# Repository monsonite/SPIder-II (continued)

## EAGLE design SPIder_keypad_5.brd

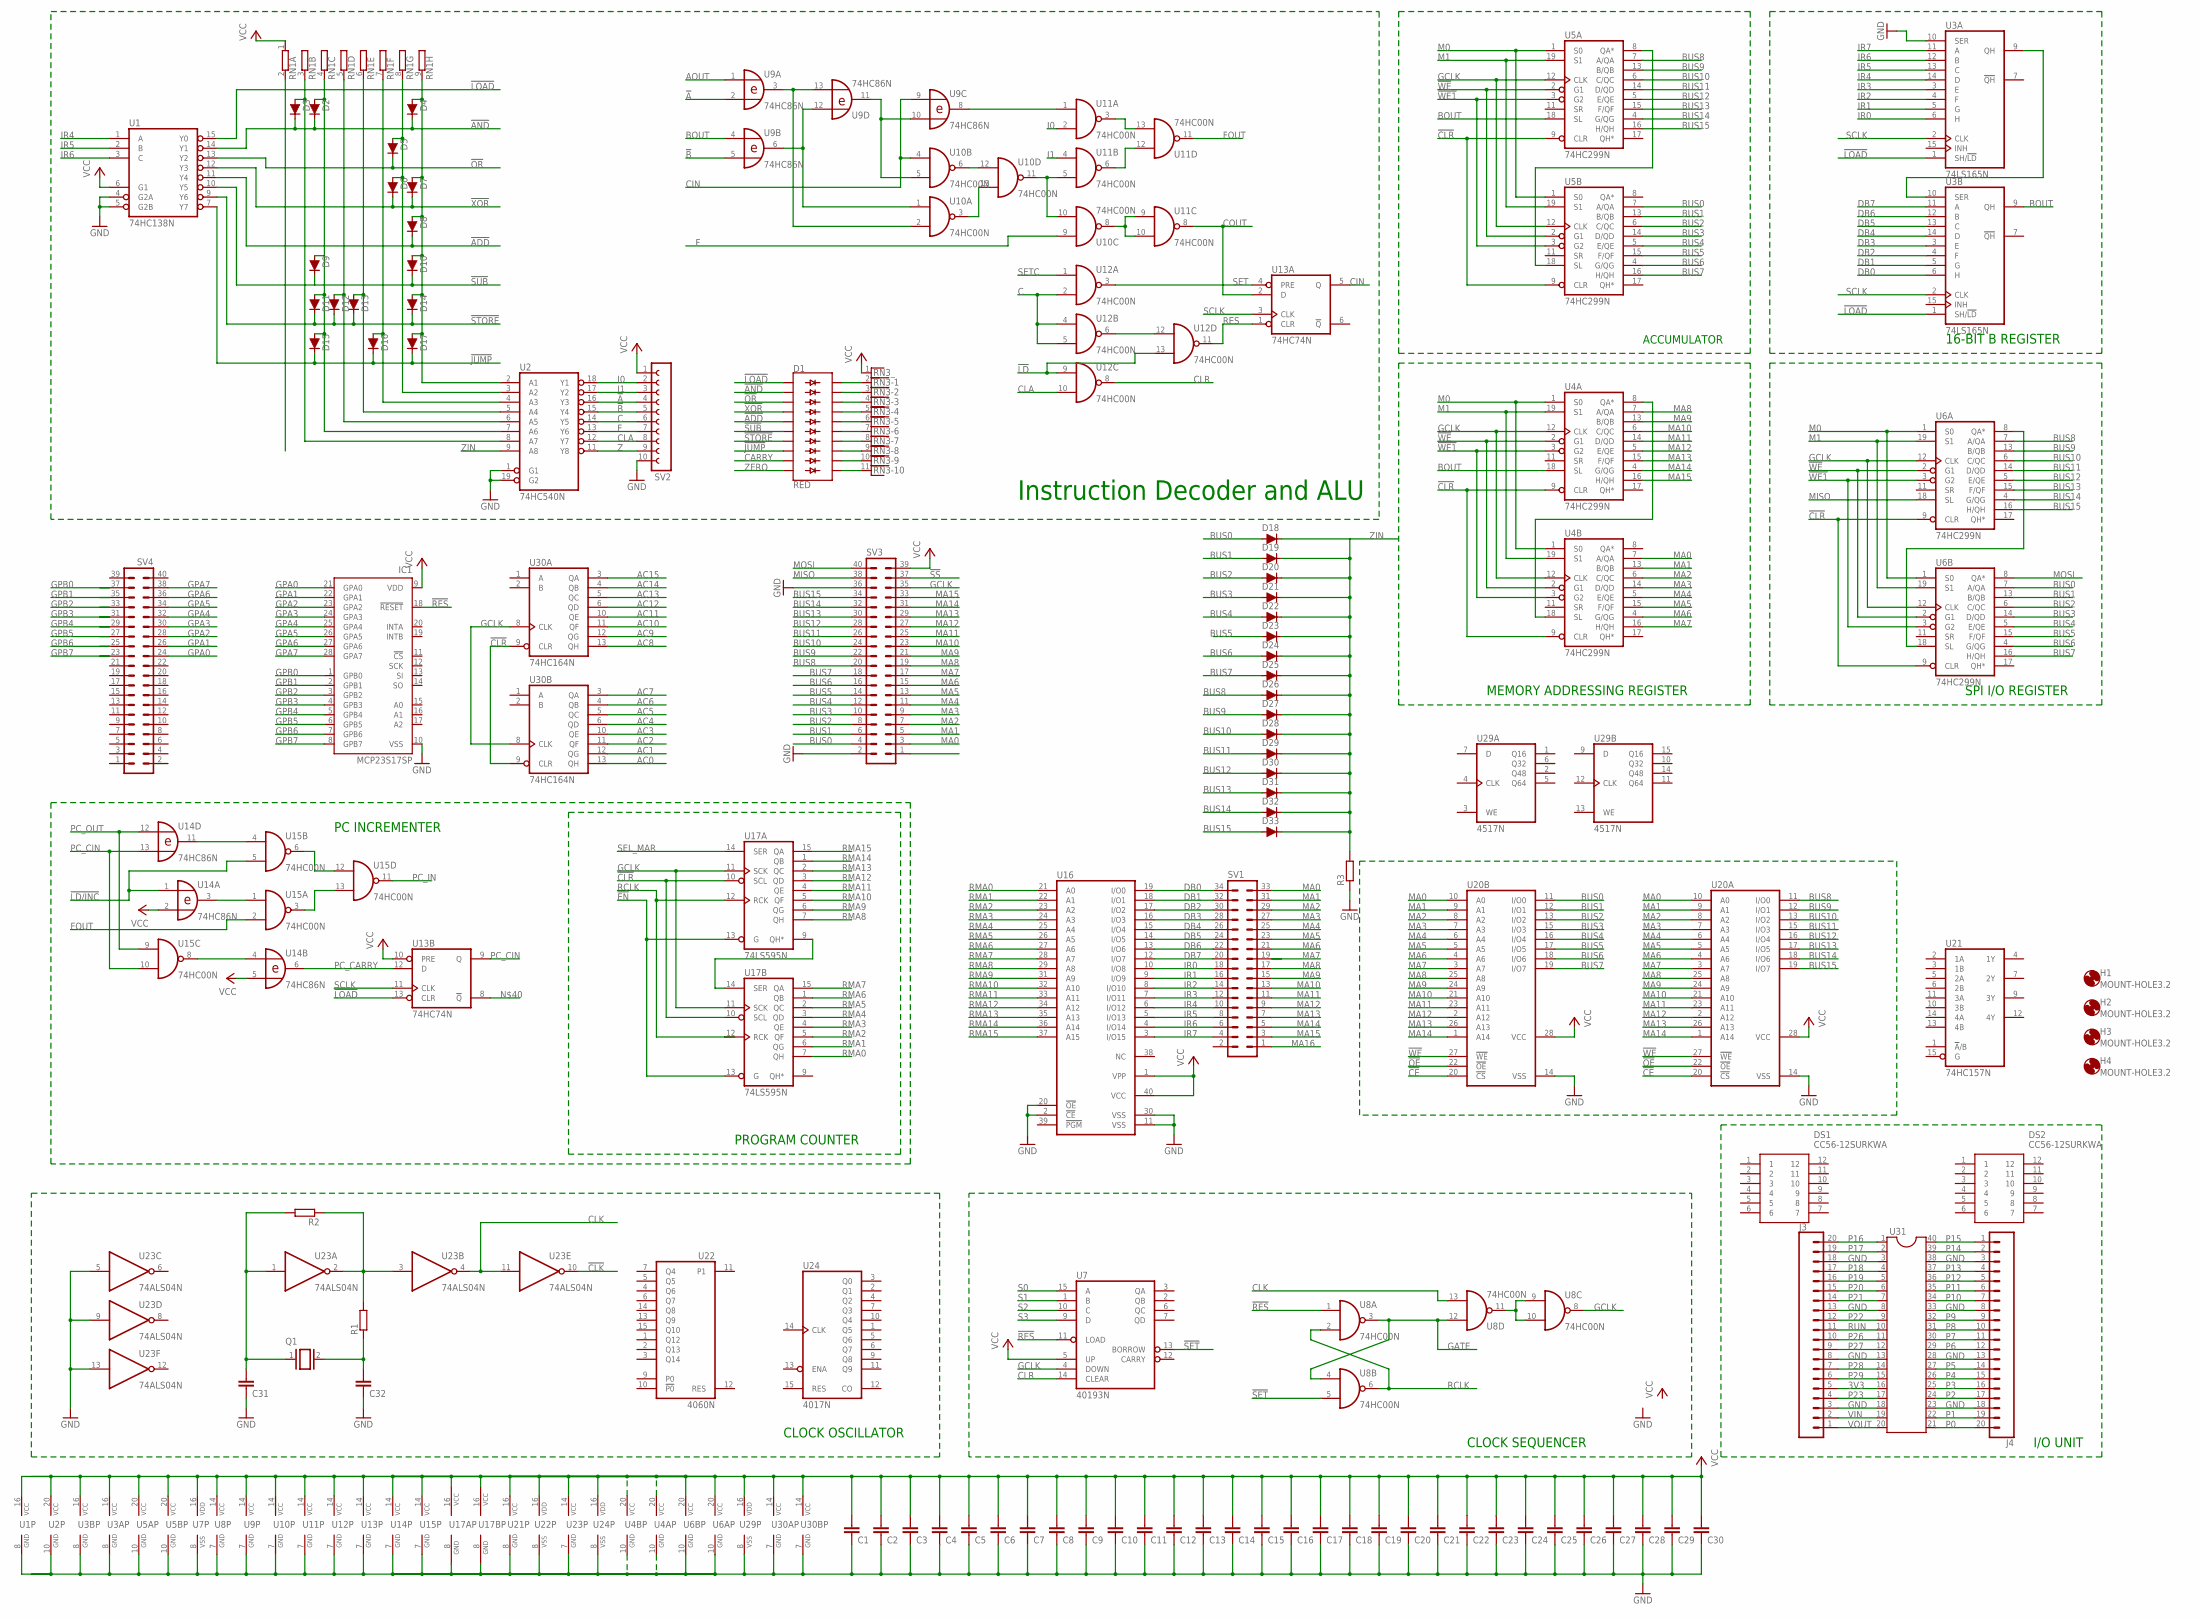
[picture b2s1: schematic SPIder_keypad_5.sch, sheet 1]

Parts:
C1, C2, C3, C4, C5, C6, C7, C8, C9, C10, C11, C12, C13, C14, C15, C16, C17, C18, C19, C20, C21, C22, C23, C24, C25, C26, C27, C28, C29, C30, C31, C32: C-EU025-024X044; C025-024X044
D1: RED; LED_BARGRAPH_10
D2, D3, D4, D5, D6, D7, D8, D9, D10, D11, D12, D13, D14, D15, D16, D17, D19, D20, D21, D22, D23, D24, D25, D26, D27, D28, D29, D30, D31, D32, D33: 200mA/100V/1V; DIODE-1N4148
D18: 200mA/100V/1V; DIODE-1N4148-KIT
DS1, DS2: CC56-12SURKWA; DIPS1524W75P254L5030H810Q12N
H1, H2, H3, H4: MOUNT-HOLE3.2; 3,2
IC1: MCP23S17SP; DIL28-3
J3, J4: CONN_20SPECIAL; 1X20_LOCK_SPECIAL
Q1: XTAL/S; QS
R1, R2, R3: R-EU_0204/5; 0204/5
RN1: GE08R; SIL9
RN3: RNX10; RN-11
SV1: MA17-2
SV2: FE10-1; FE10
SV3, SV4: MA20-2
U1: 74HC138N; DIL16
U2: 74HC540N; DIL20
U3A, U3B: 74LS165N; DIL16
U4A, U4B, U5A, U5B, U6A, U6B: 74HC299N; DIL20
U7: 40193N; DIL16
U8, U10, U11, U12, U15: 74HC00N; DIL14
U9, U14: 74HC86N; DIL14
U13: 74HC74N; DIL14
U16: 27C1024HG; DIL40
U17A, U17B: 74LS595N; DIL16
U20A, U20B: 62256P; DIL28-6
U21: 74HC157N; DIL16
U22: 4060N; DIL16
U23: 74ALS04N; DIL14
U24: 4017N; DIL16
U29: 4517N; DIL16
U30A, U30B: 74HC164N; DIL14
U31: DIL40

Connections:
3V3: J3.5, U31.16
!A: SV2.4, U2.16 (Y3), U9.2 (I1)
!ADD: D1.5 (A4), D8.C, U1.11 (Y4)
!AND: D1.2 (A1), D2.C, D3.C, D4.C, U1.14 (Y1)
!B: SV2.5, U2.15 (Y4), U9.5 (I1)
!CE: U20A.20 (!CS), U20B.20 (!CS)
!CLK: U23.10 (O)
!CLR: U4A.9 (CLR), U4B.9 (CLR), U5A.9 (CLR), U5B.9 (CLR), U6A.9 (CLR), U6B.9 (CLR), U17A.10 (SCL), U17B.10 (SCL), U30A.9 (CLR), U30B.9 (CLR)
!EN: U17A.13 (G), U17B.13 (G)
!JUMP: D1.8 (A7), D15.C, D16.C, D17.C, U1.7 (Y7)
!LD: U12.9 (I0), U12.13 (I1)
!LD/INC: U14.1 (I0), U15.5 (I1)
!LOAD: D1.1 (A), U1.15 (Y0), U3A.1 (SH/!LD), U3B.1 (SH/!LD), U13.13 (CLR)
!OE: U20A.22 (!OE), U20B.22 (!OE)
!OR: D1.3 (A2), D5.C, U1.13 (Y2)
!RES: IC1.18 (!RESET), U7.11 (LOAD), U8.1 (I0)
!SET: U7.13 (BORROW), U8.5 (I1)
!SS: SV3.37
!STORE: D1.7 (A6), D11.C, D12.C, D13.C, D14.C, U1.9 (Y6)
!SUB: D1.6 (A5), D9.C, D10.C, U1.10 (Y5)
!WE: U4A.2 (G1), U4B.2 (G1), U5A.2 (G1), U5B.2 (G1), U6A.2 (G1), U6B.2 (G1), U20A.27 (!WE), U20B.27 (!WE)
!WE1: U4A.3 (G2), U4B.3 (G2), U5A.3 (G2), U5B.3 (G2), U6A.3 (G2), U6B.3 (G2)
!XOR: D1.4 (A3), D6.C, D7.C, U1.12 (Y3)
AC0: U30B.13 (QH); also elsewhere on the board
AC1: U30B.12 (QG); also elsewhere on the board
AC2: U30B.11 (QF); also elsewhere on the board
AC3: U30B.10 (QE); also elsewhere on the board
AC4: U30B.6 (QD); also elsewhere on the board
AC5: U30B.5 (QC); also elsewhere on the board
AC6: U30B.4 (QB); also elsewhere on the board
AC7: U30B.3 (QA); also elsewhere on the board
AC8: U30A.13 (QH); also elsewhere on the board
AC9: U30A.12 (QG); also elsewhere on the board
AC10: U30A.11 (QF); also elsewhere on the board
AC11: U30A.10 (QE); also elsewhere on the board
AC12: U30A.6 (QD); also elsewhere on the board
AC13: U30A.5 (QC); also elsewhere on the board
AC14: U30A.4 (QB)
AC15: U30A.3 (QA); also elsewhere on the board
AOUT: U9.1 (I0)
BOUT: U3B.9 (QH), U4A.18 (SL), U5A.18 (SL), U9.4 (I0)
BUS0: D18.A, SV3.4, U5B.7 (A/QA), U6B.7 (A/QA), U20B.11 (I/O0)
BUS1: D19.A, SV3.6, U5B.13 (B/QB), U6B.13 (B/QB), U20B.12 (I/O1)
BUS2: D20.A, SV3.8, U5B.6 (C/QC), U6B.6 (C/QC), U20B.13 (I/O2)
BUS3: D21.A, SV3.10, U5B.14 (D/QD), U6B.14 (D/QD), U20B.15 (I/O3)
BUS4: D22.A, SV3.12, U5B.5 (E/QE), U6B.5 (E/QE), U20B.16 (I/O4)
BUS5: D23.A, SV3.14, U5B.15 (F/QF), U6B.15 (F/QF), U20B.17 (I/O5)
BUS6: D24.A, SV3.16, U5B.4 (G/QG), U6B.4 (G/QG), U20B.18 (I/O6)
BUS7: D25.A, SV3.18, U5B.16 (H/QH), U6B.16 (H/QH), U20B.19 (I/O7)
BUS8: D26.A, SV3.20, U5A.7 (A/QA), U6A.7 (A/QA), U20A.11 (I/O0)
BUS9: D27.A, SV3.22, U5A.13 (B/QB), U6A.13 (B/QB), U20A.12 (I/O1)
BUS10: D28.A, SV3.24, U5A.6 (C/QC), U6A.6 (C/QC), U20A.13 (I/O2)
BUS11: D29.A, SV3.26, U5A.14 (D/QD), U6A.14 (D/QD), U20A.15 (I/O3)
BUS12: D30.A, SV3.28, U5A.5 (E/QE), U6A.5 (E/QE), U20A.16 (I/O4)
BUS13: D31.A, SV3.30, U5A.15 (F/QF), U6A.15 (F/QF), U20A.17 (I/O5)
BUS14: D32.A, SV3.32, U5A.4 (G/QG), U6A.4 (G/QG), U20A.18 (I/O6)
BUS15: D33.A, SV3.34, U5A.16 (H/QH), U6A.16 (H/QH), U20A.19 (I/O7)
C: SV2.6, U2.14 (Y5), U12.2 (I1), U12.4 (I0), U12.5 (I1)
CARRY: D1.9 (A8); also elsewhere on the board
CIN: U9.9 (I0), U10.4 (I0), U13.5 (Q)
CLA: SV2.8, U2.12 (Y7), U12.10 (I1)
CLK: U8.13 (I1), U23.4 (O), U23.11 (I)
CLR: U7.14 (CLEAR), U12.8 (O)
COUT: U11.8 (O), U13.2 (D)
DB0: SV1.34, U3B.6 (H), U16.19 (I/O0)
DB1: SV1.32, U3B.5 (G), U16.18 (I/O1)
DB2: SV1.30, U3B.4 (F), U16.17 (I/O2)
DB3: SV1.28, U3B.3 (E), U16.16 (I/O3)
DB4: SV1.26, U3B.14 (D), U16.15 (I/O4)
DB5: SV1.24, U3B.13 (C), U16.14 (I/O5)
DB6: SV1.22, U3B.12 (B), U16.13 (I/O6)
DB7: SV1.20, U3B.11 (A), U16.12 (I/O7)
F: SV2.7, U2.13 (Y6), U10.9 (I0)
FOUT: U11.11 (O), U15.2 (I1)
GATE: U8.3 (O), U8.4 (I0), U8.12 (I0)
GCLK: SV3.35, U4A.12 (CLK), U4B.12 (CLK), U5A.12 (CLK), U5B.12 (CLK), U6A.12 (CLK), U6B.12 (CLK), U7.4 (DOWN), U8.8 (O), U17A.11 (SCK), U17B.11 (SCK), U30A.8 (CLK), U30B.8 (CLK)
GND: C1.1, C2.1, C3.1, C4.1, C5.1, C6.1, C7.1, C8.1, C9.1, C10.1, C11.1, C12.1, C13.1, C14.1, C15.1, C16.1, C17.1, C18.1, C19.1, C20.1, C21.1, C22.1, C23.1, C24.1, C25.1, C26.1, C27.1, C28.1, C29.1, C30.1, C31.1, C32.1, IC1.10 (VSS), J3.3, J3.8, J3.13, J3.18, J4.3, J4.8, J4.13, J4.18, R3.1, SV2.10, SV3.2, U1.4 (G2A), U1.5 (G2B), U1.8 (GND), U2.1 (G1), U2.10 (GND), U2.19 (G2), U3A.8 (GND), U3B.8 (GND), U4A.10 (GND), U4B.10 (GND), U5A.10 (GND), U5B.10 (GND), U6A.10 (GND), U6B.10 (GND), U7.8 (VSS), U8.7 (GND), U9.7 (GND), U10.7 (GND), U11.7 (GND), U12.7 (GND), U13.7 (GND), U14.7 (GND), U15.7 (GND), U16.2 (!CE), U16.11 (VSS), U16.20 (!OE), U16.30 (VSS), U17A.8 (GND), U17B.8 (GND), U20A.14 (VSS), U20B.14 (VSS), U21.8 (GND), U22.8 (VSS), U23.5 (I), U23.7 (GND), U23.9 (I), U23.13 (I), U24.8 (VSS), U29.8 (VSS), U30A.7 (GND), U30B.7 (GND), U31.3, U31.8, U31.13, U31.18, U31.23, U31.28, U31.33, U31.38; also elsewhere on the board
GPA0: IC1.21 (GPA0), SV4.24
GPA1: IC1.22 (GPA1), SV4.26
GPA2: IC1.23 (GPA2), SV4.28
GPA3: IC1.24 (GPA3), SV4.30
GPA4: IC1.25 (GPA4), SV4.32
GPA5: IC1.26 (GPA5), SV4.34
GPA6: IC1.27 (GPA6), SV4.36
GPA7: IC1.28 (GPA7), SV4.38
GPB0: IC1.1 (GPB0), SV4.37
GPB1: IC1.2 (GPB1), SV4.35
GPB2: IC1.3 (GPB2), SV4.33
GPB3: IC1.4 (GPB3), SV4.31
GPB4: IC1.5 (GPB4), SV4.29
GPB5: IC1.6 (GPB5), SV4.27
GPB6: IC1.7 (GPB6), SV4.25
GPB7: IC1.8 (GPB7), SV4.23
I0: SV2.2, U2.18 (Y1), U11.2 (I1)
I1: SV2.3, U2.17 (Y2), U11.4 (I0)
IR0: SV1.18, U3A.6 (H), U16.10 (I/O8)
IR1: SV1.16, U3A.5 (G), U16.9 (I/O9)
IR2: SV1.14, U3A.4 (F), U16.8 (I/O10)
IR3: SV1.12, U3A.3 (E), U16.7 (I/O11)
IR4: SV1.10, U1.1 (A), U3A.14 (D), U16.6 (I/O12)
IR5: SV1.8, U1.2 (B), U3A.13 (C), U16.5 (I/O13)
IR6: SV1.6, U1.3 (C), U3A.12 (B), U16.4 (I/O14)
IR7: SV1.4, U3A.11 (A), U16.3 (I/O15)
M0: U4A.1 (S0), U4B.1 (S0), U5A.1 (S0), U5B.1 (S0), U6A.1 (S0), U6B.1 (S0)
M1: U4A.19 (S1), U4B.19 (S1), U5A.19 (S1), U5B.19 (S1), U6A.19 (S1), U6B.19 (S1)
MA0: SV1.33, SV3.3, U4B.7 (A/QA), U20A.10 (A0), U20B.10 (A0)
MA1: SV1.31, SV3.5, U4B.13 (B/QB), U20A.9 (A1), U20B.9 (A1)
MA2: SV1.29, SV3.7, U4B.6 (C/QC), U20A.8 (A2), U20B.8 (A2)
MA3: SV1.27, SV3.9, U4B.14 (D/QD), U20A.7 (A3), U20B.7 (A3)
MA4: SV1.25, SV3.11, U4B.5 (E/QE), U20A.6 (A4), U20B.6 (A4)
MA5: SV1.23, SV3.13, U4B.15 (F/QF), U20A.5 (A5), U20B.5 (A5)
MA6: SV1.21, SV3.15, U4B.4 (G/QG), U20A.4 (A6), U20B.4 (A6)
MA7: SV1.19, SV3.17, U4B.16 (H/QH), U20A.3 (A7), U20B.3 (A7)
MA8: SV1.17, SV3.19, U4A.7 (A/QA), U20A.25 (A8), U20B.25 (A8)
MA9: SV1.15, SV3.21, U4A.13 (B/QB), U20A.24 (A9), U20B.24 (A9)
MA10: SV1.13, SV3.23, U4A.6 (C/QC), U20A.21 (A10), U20B.21 (A10)
MA11: SV1.11, SV3.25, U4A.14 (D/QD), U20A.23 (A11), U20B.23 (A11)
MA12: SV1.9, SV3.27, U4A.5 (E/QE), U20A.2 (A12), U20B.2 (A12)
MA13: SV1.7, SV3.29, U4A.15 (F/QF), U20A.26 (A13), U20B.26 (A13)
MA14: SV1.5, SV3.31, U4A.4 (G/QG), U20A.1 (A14), U20B.1 (A14)
MA15: SV1.3, SV3.33, U4A.16 (H/QH)
MA16: SV1.1
MISO: SV3.38, U6A.18 (SL)
MOSI: SV3.40, U6B.8 (QA*)
unnamed: U3A.9 (QH), U3B.10 (SER)
unnamed: U17A.9 (QH*), U17B.14 (SER)
unnamed: U10.8 (O), U11.9 (I0), U11.10 (I1)
unnamed: U12.6 (O), U12.12 (I0)
unnamed: U4A.8 (QA*), U4B.18 (SL)
unnamed: U8.9 (I0), U8.10 (I1), U8.11 (O)
unnamed: U9.3 (O), U9.13 (I1), U10.2 (I1)
unnamed: U9.6 (O), U9.12 (I0), U10.1 (I0)
unnamed: U9.10 (I1), U9.11 (O), U10.5 (I1)
unnamed: U10.6 (O), U10.12 (I0)
unnamed: U10.3 (O), U10.13 (I1)
unnamed: U10.10 (I1), U10.11 (O), U11.5 (I1)
unnamed: U11.3 (O), U11.13 (I1)
unnamed: U11.6 (O), U11.12 (I0)
unnamed: U9.8 (O), U11.1 (I0)
unnamed: U6A.8 (QA*), U6B.18 (SL)
unnamed: D3.A, RN1.3 (2), U2.8 (A7)
unnamed: D2.A, D9.A, D11.A, D15.A, RN1.4 (2), U2.7 (A6)
unnamed: U5A.8 (QA*), U5B.18 (SL)
unnamed: D12.A, RN1.5 (2), U2.6 (A5)
unnamed: D1.20 (C), RN3.2
unnamed: D1.19 (C1), RN3.3
unnamed: U15.3 (O), U15.13 (I1)
unnamed: U15.6 (O), U15.12 (I0)
unnamed: D13.A, RN1.6 (2), U2.5 (A4)
unnamed: U14.11 (O), U15.4 (I0)
unnamed: U14.4 (I0), U15.8 (O)
unnamed: C31.2, Q1.1, R2.2, U23.1 (I)
unnamed: C32.2, Q1.2, R1.1
unnamed: U14.3 (O), U15.1 (I0)
unnamed: R1.2, R2.1, U23.2 (O), U23.3 (I)
unnamed: D16.A, RN1.7 (2), U2.4 (A3)
unnamed: D1.18 (C2), RN3.4
unnamed: D1.17 (C3), RN3.5
unnamed: D1.16 (C4), RN3.6
unnamed: D1.15 (C5), RN3.7
unnamed: D1.14 (C6), RN3.8
unnamed: D1.13 (C7), RN3.9
unnamed: D1.12 (C8), RN3.10
unnamed: D1.11 (C9), RN3.11
unnamed: D5.A, D6.A, RN1.8 (2), U2.3 (A2)
unnamed: D4.A, D7.A, D8.A, D10.A, D14.A, D17.A, RN1.9 (2), U2.2 (A1)
P0: J4.20, U31.21
P1: J4.19, U31.22
P2: J4.17, U31.24
P3: J4.16, U31.25
P4: J4.15, U31.26
P5: J4.14, U31.27
P6: J4.12, U31.29
P7: J4.11, U31.30
P8: J4.10, U31.31
P9: J4.9, U31.32
P10: J4.7, U31.34
P11: J4.6, U31.35
P12: J4.5, U31.36
P13: J4.4, U31.37
P14: J4.2, U31.39
P15: J4.1, U31.40
P16: J3.20, U31.1
P17: J3.19, U31.2
P18: J3.17, U31.4
P19: J3.16, U31.5
P20: J3.15, U31.6
P21: J3.14, U31.7
P22: J3.12, U31.9
P23: J3.4, U31.17
P26: J3.10, U31.11
P27: J3.9, U31.12
P28: J3.7, U31.14
P29: J3.6, U31.15
PC_CARRY: U13.12 (D), U14.6 (O)
PC_CIN: U13.9 (Q), U14.13 (I1), U15.10 (I1)
PC_IN: U15.11 (O)
PC_OUT: U14.12 (I0), U15.9 (I0)
RCLK: U8.2 (I1), U8.6 (O), U17A.12 (RCK), U17B.12 (RCK)
RES: U12.11 (O), U13.1 (CLR)
RMA0: U16.21 (A0), U17B.7 (QH)
RMA1: U16.22 (A1), U17B.6 (QG)
RMA2: U16.23 (A2), U17B.5 (QF)
RMA3: U16.24 (A3), U17B.4 (QE)
RMA4: U16.25 (A4), U17B.3 (QD)
RMA5: U16.26 (A5), U17B.2 (QC)
RMA6: U16.27 (A6), U17B.1 (QB)
RMA7: U16.28 (A7), U17B.15 (QA)
RMA8: U16.29 (A8), U17A.7 (QH)
RMA9: U16.31 (A9), U17A.6 (QG)
RMA10: U16.32 (A10), U17A.5 (QF)
RMA11: U16.33 (A11), U17A.4 (QE)
RMA12: U16.34 (A12), U17A.3 (QD)
RMA13: U16.35 (A13), U17A.2 (QC)
RMA14: U16.36 (A14), U17A.1 (QB)
RMA15: U16.37 (A15), U17A.15 (QA)
RUN: J3.11, U31.10
S0: U7.15 (A)
S1: U7.1 (B)
S2: U7.10 (C)
S3: U7.9 (D)
SCLK: U3A.2 (CLK), U3B.2 (CLK), U13.3 (CLK), U13.11 (CLK)
SEL_MAR: U17A.14 (SER)
SET: U12.3 (O), U13.4 (PRE)
SETC: U12.1 (I0)
VCC: C1.2, C2.2, C3.2, C4.2, C5.2, C6.2, C7.2, C8.2, C9.2, C10.2, C11.2, C12.2, C13.2, C14.2, C15.2, C16.2, C17.2, C18.2, C19.2, C20.2, C21.2, C22.2, C23.2, C24.2, C25.2, C26.2, C27.2, C28.2, C29.2, C30.2, IC1.9 (VDD), RN1.1, RN3.1, SV2.1, SV3.39, U1.6 (G1), U1.16 (VCC), U2.20 (VCC), U3A.16 (VCC), U3B.16 (VCC), U4A.20 (VCC), U4B.20 (VCC), U5A.20 (VCC), U5B.20 (VCC), U6A.20 (VCC), U6B.20 (VCC), U7.5 (UP), U7.16 (VDD), U8.14 (VCC), U9.14 (VCC), U10.14 (VCC), U11.14 (VCC), U12.14 (VCC), U13.10 (PRE), U13.14 (VCC), U14.2 (I1), U14.5 (I1), U14.14 (VCC), U15.14 (VCC), U16.1 (VPP), U16.40 (VCC), U17A.16 (VCC), U17B.16 (VCC), U20A.28 (VCC), U20B.28 (VCC), U21.16 (VCC), U22.16 (VDD), U23.14 (VCC), U24.16 (VDD), U29.16 (VDD), U30A.14 (VCC), U30B.14 (VCC); also elsewhere on the board
VIN: J3.2, U31.19
VOUT: J3.1, U31.20
Z: SV2.9, U2.11 (Y8)
ZERO: D1.10 (A9); also elsewhere on the board
ZIN: D18.C, D19.C, D20.C, D21.C, D22.C, D23.C, D24.C, D25.C, D26.C, D27.C, D28.C, D29.C, D30.C, D31.C, D32.C, D33.C, R3.2, U2.9 (A8)

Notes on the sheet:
Instruction Decoder and ALU
PC INCREMENTER
CLOCK SEQUENCER
MEMORY ADDRESSING REGISTER
ACCUMULATOR
PROGRAM COUNTER
16-BIT B REGISTER
CLOCK OSCILLATOR
SPI I/O REGISTER
I/O UNIT

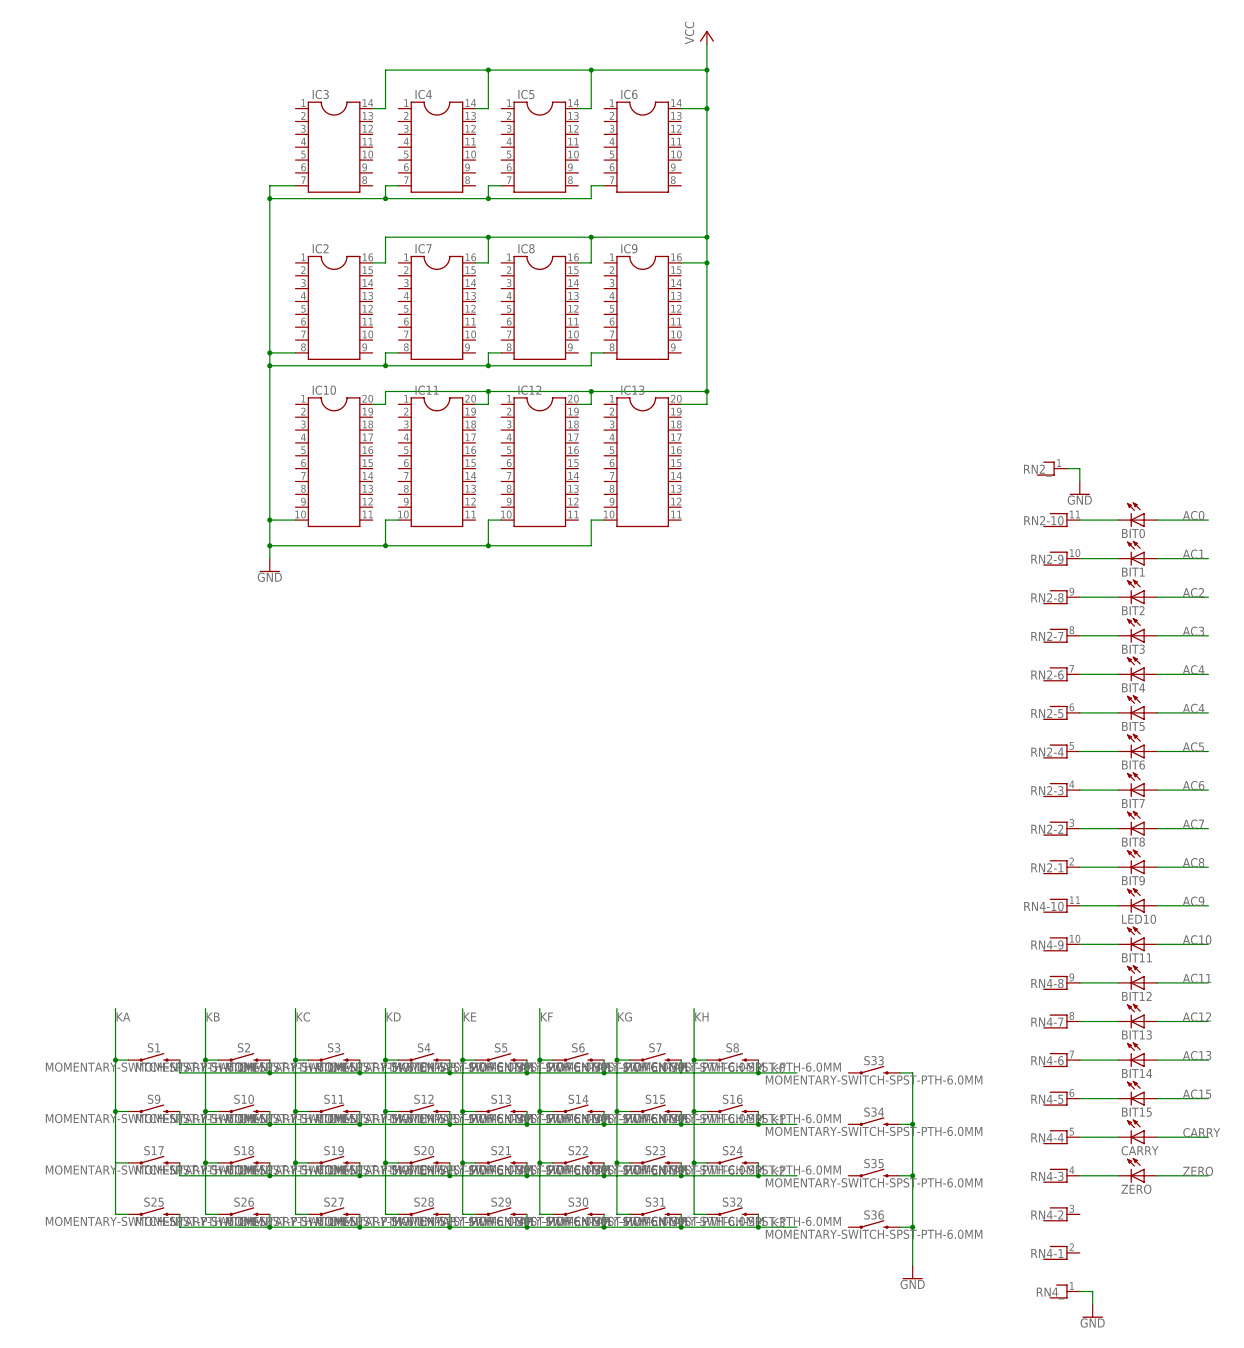
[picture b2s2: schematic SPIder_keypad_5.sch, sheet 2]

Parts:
BIT0, BIT1, BIT2, BIT3, BIT4, BIT5, BIT6, BIT7, BIT8, BIT9, BIT11, BIT12, BIT13, BIT14, BIT15: LED3MM
CARRY: LED3MM
IC2, IC7, IC8, IC9: DIL16S; SOCKET-16
IC3, IC4, IC5, IC6: DIL14S; SOCKET-14
IC10, IC11, IC12, IC13: DIL20S; SOCKET-20
LED10: LED3MM
RN2, RN4: RNX10; RN-11
S1, S2, S3, S4, S5, S6, S7, S8, S9, S10, S11, S12, S13, S14, S15, S16, S17, S18, S19, S20, S21, S22, S23, S24, S25, S26, S27, S28, S29, S30, S31, S32, S33, S34, S35, S36: MOMENTARY-SWITCH-SPST-PTH-6.0MM; TACTILE_SWITCH_PTH_6.0MM
ZERO: LED3MM

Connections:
AC0: BIT0.A; also elsewhere on the board
AC1: BIT1.A; also elsewhere on the board
AC2: BIT2.A; also elsewhere on the board
AC3: BIT3.A; also elsewhere on the board
AC4: BIT4.A, BIT5.A; also elsewhere on the board
AC5: BIT6.A; also elsewhere on the board
AC6: BIT7.A; also elsewhere on the board
AC7: BIT8.A; also elsewhere on the board
AC8: BIT9.A; also elsewhere on the board
AC9: LED10.A; also elsewhere on the board
AC10: BIT11.A; also elsewhere on the board
AC11: BIT12.A; also elsewhere on the board
AC12: BIT13.A; also elsewhere on the board
AC13: BIT14.A; also elsewhere on the board
AC15: BIT15.A; also elsewhere on the board
CARRY: CARRY.A; also elsewhere on the board
GND: IC2.8, IC3.7, IC4.7, IC5.7, IC6.7, IC7.8, IC8.8, IC9.8, IC10.10, IC11.10, IC12.10, IC13.10, RN2.1, RN4.1, S33.3 (2), S34.3 (2), S35.3 (2), S36.3 (2); also elsewhere on the board
K0: S1.3 (2), S2.3 (2), S3.3 (2), S4.3 (2), S5.3 (2), S6.3 (2), S7.3 (2), S8.3 (2)
K1: S9.3 (2), S10.3 (2), S11.3 (2), S12.3 (2), S13.3 (2), S14.3 (2), S15.3 (2), S16.3 (2)
K2: S17.3 (2), S18.3 (2), S19.3 (2), S20.3 (2), S21.3 (2), S22.3 (2), S23.3 (2), S24.3 (2)
K3: S25.3 (2), S26.3 (2), S27.3 (2), S28.3 (2), S29.3 (2), S30.3 (2), S31.3 (2), S32.3 (2)
KA: S1.1, S9.1, S17.1, S25.1
KB: S2.1, S10.1, S18.1, S26.1
KC: S3.1, S11.1, S19.1, S27.1
KD: S4.1, S12.1, S20.1, S28.1
KE: S5.1, S13.1, S21.1, S29.1
KF: S6.1, S14.1, S22.1, S30.1
KG: S7.1, S15.1, S23.1, S31.1
KH: S8.1, S16.1, S24.1, S32.1
unnamed: BIT0.K (C), RN2.11
unnamed: BIT1.K (C), RN2.10
unnamed: BIT2.K (C), RN2.9
unnamed: BIT3.K (C), RN2.8
unnamed: BIT4.K (C), RN2.7
unnamed: BIT5.K (C), RN2.6
unnamed: BIT6.K (C), RN2.5
unnamed: BIT7.K (C), RN2.4
unnamed: BIT8.K (C), RN2.3
unnamed: BIT9.K (C), RN2.2
unnamed: LED10.K (C), RN4.11
unnamed: BIT11.K (C), RN4.10
unnamed: BIT12.K (C), RN4.9
unnamed: BIT13.K (C), RN4.8
unnamed: BIT14.K (C), RN4.7
unnamed: BIT15.K (C), RN4.6
unnamed: CARRY.K (C), RN4.5
unnamed: RN4.4, ZERO.K (C)
VCC: IC2.16, IC3.14, IC4.14, IC5.14, IC6.14, IC7.16, IC8.16, IC9.16, IC10.20, IC11.20, IC12.20, IC13.20; also elsewhere on the board
ZERO: ZERO.A; also elsewhere on the board

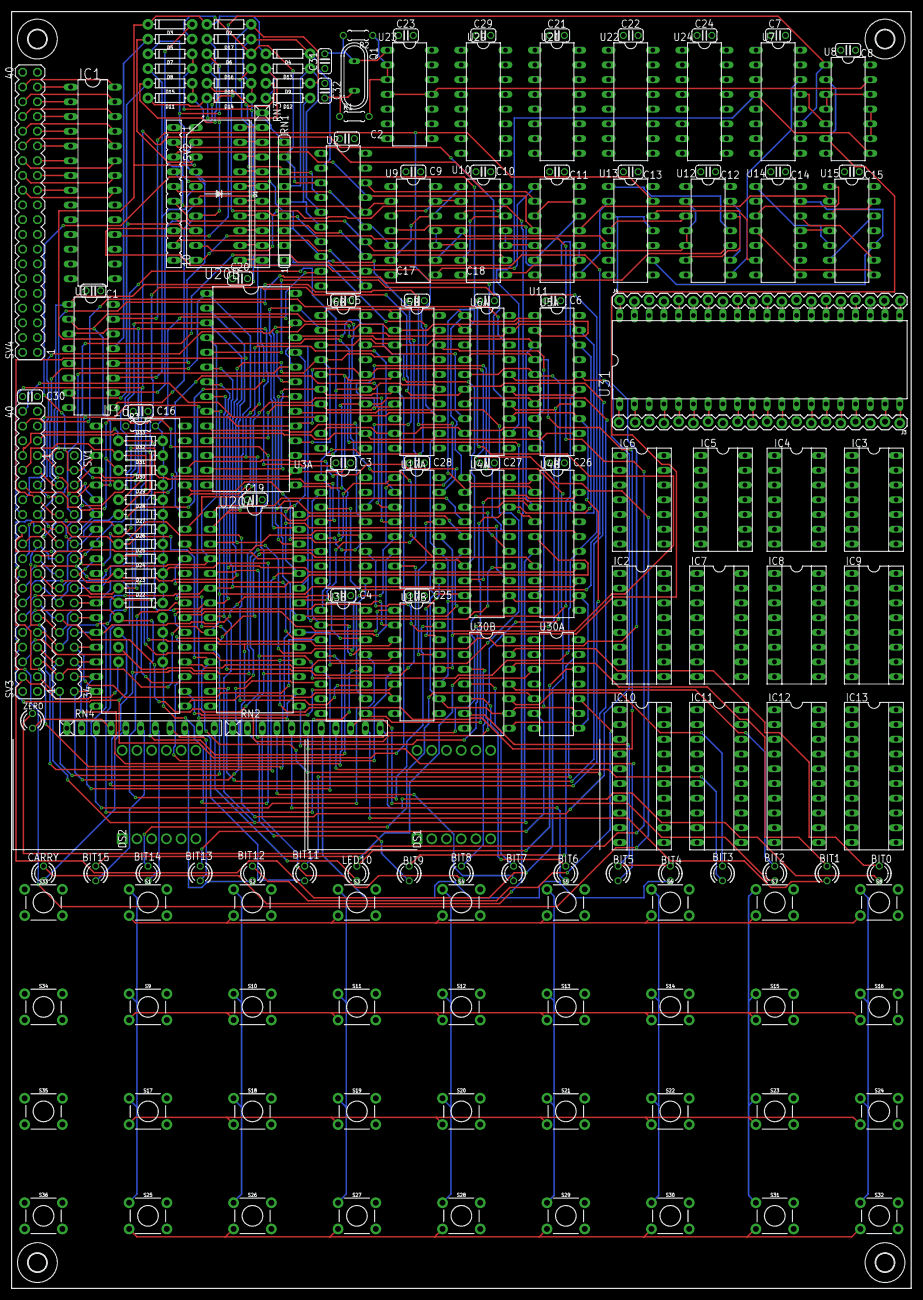
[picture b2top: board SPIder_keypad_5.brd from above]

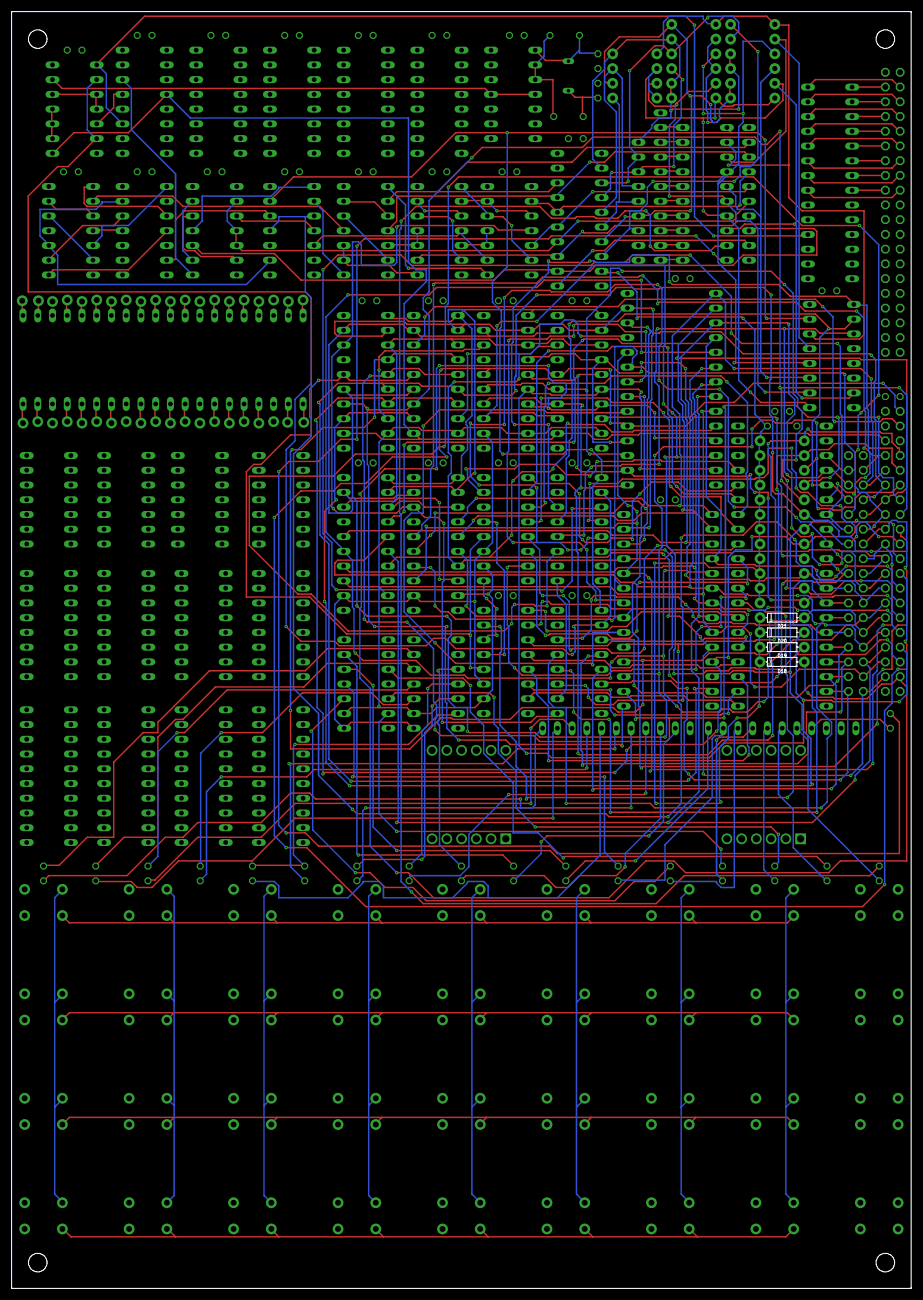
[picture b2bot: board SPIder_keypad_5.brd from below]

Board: 4 copper layers, 155.0 x 220.0 mm, 184 parts (4 on the bottom side), 249 nets.
